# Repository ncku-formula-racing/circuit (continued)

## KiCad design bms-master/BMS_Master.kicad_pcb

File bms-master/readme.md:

# BMS Master board PCB
NCKU Formula racing 2025  
BMS Master using TI's BQ79600-Q1 as communication module and STM32F103C8T6 as MCU

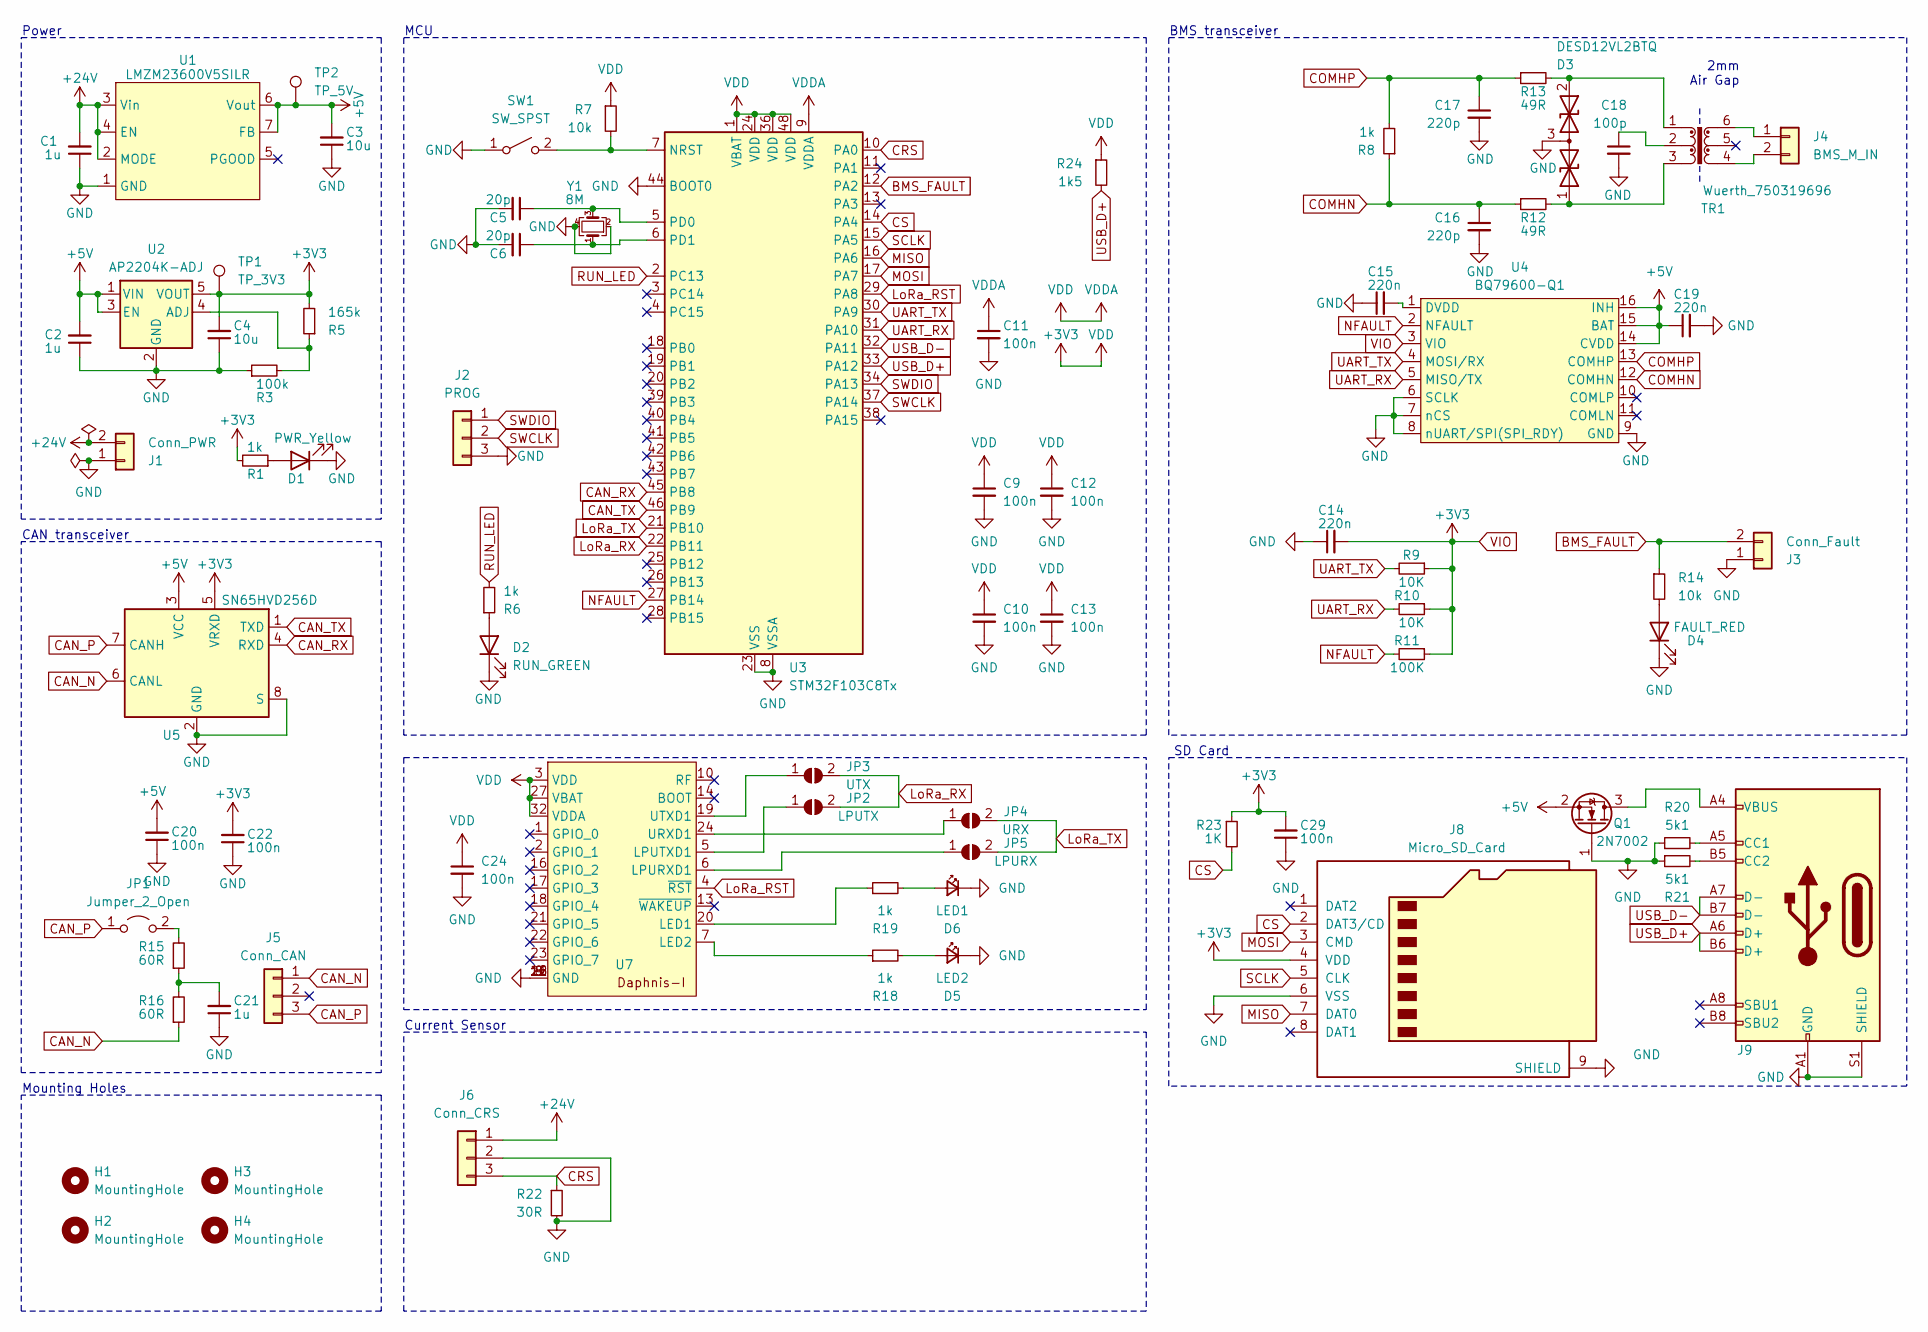
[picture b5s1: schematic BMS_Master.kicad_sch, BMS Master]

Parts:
C1, C2, C21: 1u; C_0603_1608Metric
C3, C4: 10u; C_0805_2012Metric
C5, C6: 20p; C_0603_1608Metric
C9, C10, C11, C12, C13, C20, C22, C24, C29: 100n; C_0603_1608Metric
C14, C15, C19: 220n; C_0603_1608Metric
C16, C17: 220p; C_0603_1608Metric
C18: 100p; C_0603_1608Metric
D1: PWR_Yellow; LED_0805_2012Metric
D2: RUN_GREEN; LED_0805_2012Metric
D3: DESD12VL2BTQ; SOT-23
D4: FAULT_RED; LED_0805_2012Metric
D5: LED2; LED_0805_2012Metric
D6: LED1; LED_0805_2012Metric
H1, H2, H3, H4: MountingHole; MountingHole_3.2mm_M3_DIN965
J1: Conn_PWR; JST_XH_B2B-XH-A_1x02_P2.50mm_Vertical
J2: PROG; PinHeader_1x03_P2.54mm_Vertical
J3: Conn_Fault; JST_XH_B2B-XH-A_1x02_P2.50mm_Vertical
J4: BMS_M_IN; Molex_Micro-Fit_3.0_43650-0200_1x02_P3.00mm_Horizontal
J5: Conn_CAN; JST_XH_B3B-XH-A_1x03_P2.50mm_Vertical
J6: Conn_CRS; JST_XH_B3B-XH-A_1x03_P2.50mm_Vertical
J8: Micro_SD_Card; microSD_HC_Molex_47219-2001
J9: USB_C_Receptacle_USB2.0_16P; USB_C_Receptacle_Palconn_UTC16-G
JP1: Jumper_2_Open; TestPoint_2Pads_Pitch2.54mm_Drill0.8mm
JP2: LPUTX; SolderJumper-2_P1.3mm_Open_RoundedPad1.0x1.5mm
JP3: UTX; SolderJumper-2_P1.3mm_Open_RoundedPad1.0x1.5mm
JP4: URX; SolderJumper-2_P1.3mm_Open_RoundedPad1.0x1.5mm
JP5: LPURX; SolderJumper-2_P1.3mm_Open_RoundedPad1.0x1.5mm
Q1: 2N7002; SOT-23
R1, R6, R8, R18, R19: 1k; R_0603_1608Metric
R3: 100k; R_0603_1608Metric
R5: 165k; R_0603_1608Metric
R7, R14: 10k; R_0603_1608Metric
R9, R10: 10K; R_0603_1608Metric
R11: 100K; R_0603_1608Metric
R12, R13: 49R; R_0603_1608Metric
R15, R16: 60R; R_0603_1608Metric
R20, R21: 5k1; R_0603_1608Metric_Pad0.98x0.95mm_HandSolder
R22: 30R; R_0603_1608Metric
R23: 1K; R_0603_1608Metric
R24: 1k5; R_0603_1608Metric
SW1: SW_SPST; SW_SPST_FSMSM
TP1: TP_3V3; Pin_D1.0mm_L10.0mm
TP2: TP_5V; Pin_D1.0mm_L10.0mm
TR1: Wuerth_750319696; Transformer_Wuerth_750315371
U1: LMZM23600V5SILR; MODULE_LMZM23601V5SILR
U2: AP2204K-ADJ; SOT-23-5
U3: STM32F103C8Tx; LQFP-48_7x7mm_P0.5mm
U4: BQ79600-Q1; TSSOP-16_4.4x5mm_P0.65mm
U5: SN65HVD256D; SOIC-8_3.9x4.9mm_P1.27mm
U7: Daphnis-I
Y1: 8M; Crystal_SMD_SeikoEpson_FA238-4Pin_3.2x2.5mm

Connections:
+5V: C2.2, C3.2, C19.1, C20.2, Q1.2 (S), TP2.1, U1.6 (Vout), U1.7 (FB), U2.1 (VIN), U2.3 (EN), U4.14 (CVDD), U4.15 (BAT), U4.16 (INH), U5.3 (VCC)
+24V: C1.2, J1.2, J6.1, U1.2 (MODE), U1.3 (Vin), U1.4 (EN)
BMS_FAULT: J3.2, R14.1, U3.12 (PA2)
CAN_N: J5.1, R16.1, U5.6 (CANL)
CAN_P: J5.3, JP1.1 (A), U5.7 (CANH)
CAN_RX: U3.45 (PB8), U5.4 (RXD)
CAN_TX: U3.46 (PB9), U5.1 (TXD)
COMHN: C16.1, R8.1, R12.1, U4.12 (COMHN)
COMHP: C17.1, R8.2, R13.1, U4.13 (COMHP)
CRS: J6.3, R22.1, U3.10 (PA0)
CS: J8.2 (DAT3/CD), R23.2, U3.14 (PA4)
GND: C1.1, C2.1, C3.1, C4.1, C5.2, C6.2, C9.2, C10.2, C11.2, C12.2, C13.2, C14.1, C15.1, C16.2, C17.2, C18.2, C19.2, C20.1, C21.1, C22.1, C24.2, C29.1, D1.1 (K), D2.1 (K), D3.3 (common), D4.1 (K), D5.1 (K), D6.1 (K), J1.1, J2.3, J3.1, J6.2, J8.6 (VSS), J8.9 (SHIELD), J9.A1 (GND), J9.A12 (GND), J9.B1 (GND), J9.B12 (GND), J9.S1 (SHIELD), Q1.1 (G), R3.1, R20.1, R21.1, R22.2, SW1.1 (A), U1.1 (GND), U1.11, U2.2 (GND), U3.8 (VSSA), U3.23 (VSS), U3.35 (VSS), U3.44 (BOOT0), U3.47 (VSS), U4.6 (SCLK), U4.7 (nCS), U4.8 (nUART/SPI(SPI_RDY)), U4.9 (GND), U5.2 (GND), U5.8 (S), U7.8 (GND), U7.9 (GND), U7.11 (GND), U7.12 (GND), U7.15 (GND), U7.26 (GND), Y1.2, Y1.4
LoRa_RST: U3.29 (PA8), U7.4 (~RST)
LoRa_RX: JP2.2 (B), JP3.2 (B), U3.22 (PB11)
LoRa_TX: JP4.2 (B), JP5.2 (B), U3.21 (PB10)
MISO: J8.7 (DAT0), U3.16 (PA6)
MOSI: J8.3 (CMD), U3.17 (PA7)
NFAULT: R11.2, U3.27 (PB14), U4.2 (NFAULT)
unnamed: C18.1, TR1.2
unnamed: C21.2, R15.1, R16.2
unnamed: D1.2 (A), R1.1
unnamed: D2.2 (A), R6.1
unnamed: D3.1 (A1), R12.2, TR1.3
unnamed: D3.2 (A2), R13.2, TR1.1
unnamed: D4.2 (A), R14.2
unnamed: D5.2 (A), R18.2
unnamed: D6.2 (A), R19.2
unnamed: J4.1, TR1.6
unnamed: J4.2, TR1.4
unnamed: J9.A5 (CC1), R20.2
unnamed: J9.B5 (CC2), R21.2
unnamed: JP1.2 (B), R15.2
unnamed: JP2.1 (A), U7.5 (LPUTXD1)
unnamed: JP3.1 (A), U7.19 (UTXD1)
unnamed: JP4.1 (A), U7.24 (URXD1)
unnamed: JP5.1 (A), U7.6 (LPURXD1)
unnamed: J9.A4 (VBUS), J9.A9 (VBUS), J9.B4 (VBUS), J9.B9 (VBUS), Q1.3 (D)
unnamed: R7.2, SW1.2 (B), U3.7 (NRST)
unnamed: R3.2, R5.1, U2.4 (ADJ)
unnamed: C5.1, U3.5 (PD0), Y1.3
unnamed: C6.1, U3.6 (PD1), Y1.1
unnamed: C15.2, U4.1 (DVDD)
unnamed: R19.1, U7.20 (LED1)
unnamed: R18.1, U7.7 (LED2)
RUN_LED: R6.2, U3.2 (PC13)
SCLK: J8.5 (CLK), U3.15 (PA5)
SWCLK: J2.2, U3.37 (PA14)
SWDIO: J2.1, U3.34 (PA13)
UART_RX: R10.2, U3.31 (PA10), U4.5 (MISO/TX)
UART_TX: R9.2, U3.30 (PA9), U4.4 (MOSI/RX)
USB_D+: J9.A6 (D+), J9.B6 (D+), R24.2, U3.33 (PA12)
USB_D-: J9.A7 (D-), J9.B7 (D-), U3.32 (PA11)
VIO: C4.2, C9.1, C10.1, C11.1, C12.1, C13.1, C14.2, C22.2, C24.1, C29.2, J8.4 (VDD), R1.2, R5.2, R7.1, R9.1, R10.1, R11.1, R23.1, R24.1, TP1.1, U2.5 (VOUT), U3.1 (VBAT), U3.9 (VDDA), U3.24 (VDD), U3.36 (VDD), U3.48 (VDD), U4.3 (VIO), U5.5 (VRXD), U7.3 (VDD), U7.27 (VBAT), U7.32 (VDDA)

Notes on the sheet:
MCU
SD Card
2mm Air Gap
Current Sensor
Mounting Holes
BMS transceiver
Power
CAN transceiver

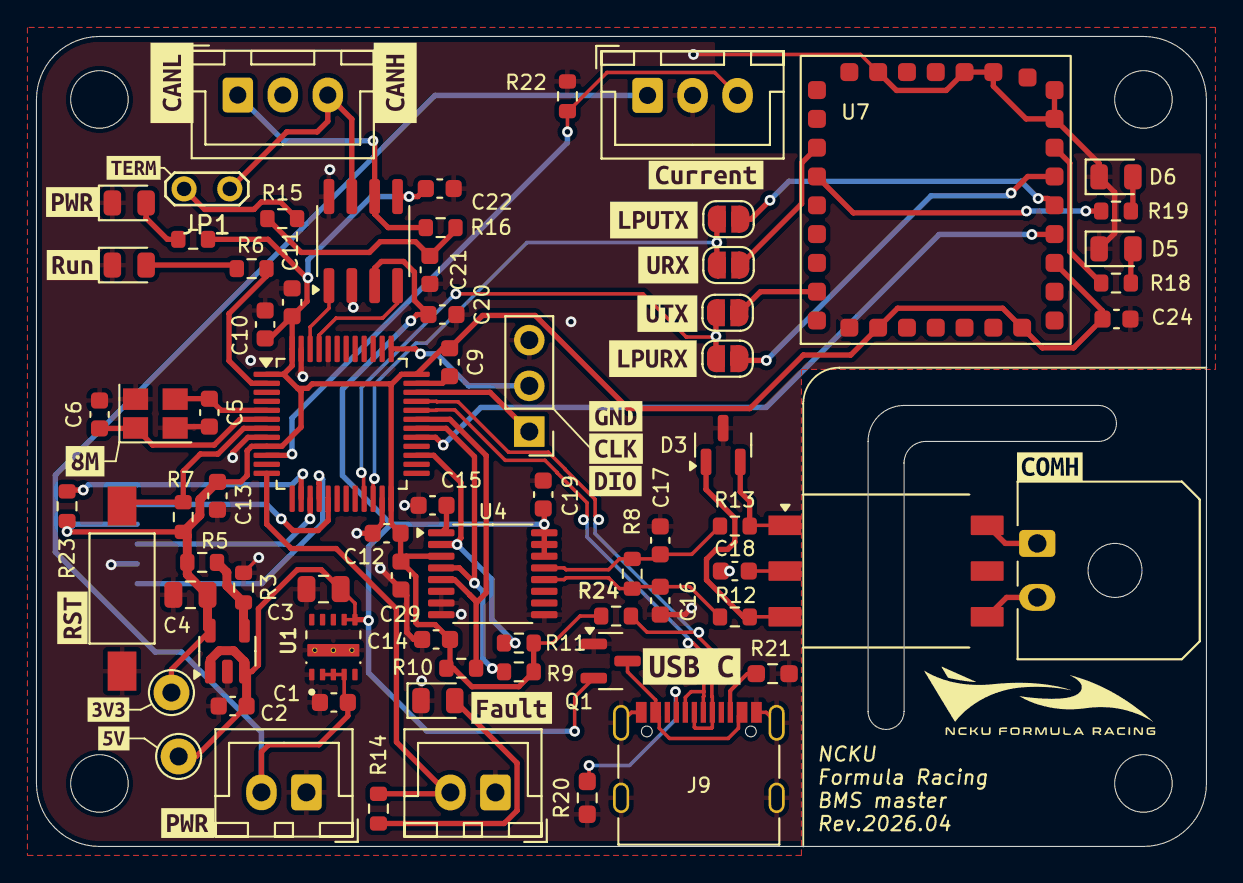
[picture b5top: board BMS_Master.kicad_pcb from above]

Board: 2 copper layers, 65.0 x 45.0 mm, 99 parts (1 on the bottom side), 53 nets.

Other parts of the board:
kibuzzard-67D6AC10: G***; kibuzzard-67D6AC10
kibuzzard-68BABEC4: G***; kibuzzard-68BABEC4
kibuzzard-68BABEE5: G***; kibuzzard-68BABEE5
kibuzzard-68BABEF1: G***; kibuzzard-68BABEF1
kibuzzard-68BABF14: G***; kibuzzard-68BABF14
kibuzzard-69EA7393: G***; kibuzzard-69EA7393
kibuzzard-69EB13FF: G***; kibuzzard-69EB13FF
kibuzzard-69EB1406: G***; kibuzzard-69EB1406
kibuzzard-679F52AD: G***; kibuzzard-679F52AD
kibuzzard-679F52BD: G***; kibuzzard-679F52BD
kibuzzard-679F55F7: G***; kibuzzard-679F55F7
kibuzzard-679F56A0: G***; kibuzzard-679F56A0
kibuzzard-679F56A8: G***; kibuzzard-679F56A8
kibuzzard-679F561D: G***; kibuzzard-679F561D
kibuzzard-679F5580: G***; kibuzzard-679F5580
kibuzzard-679F5696: G***; kibuzzard-679F5696
kibuzzard-68838A70: G***; kibuzzard-68838A70
kibuzzard-68838B09: G***; kibuzzard-68838B09
kibuzzard-68838DBE: G***; kibuzzard-68838DBE
kibuzzard-68838DC4: G***; kibuzzard-68838DC4
kibuzzard-68838E18: G***; kibuzzard-68838E18

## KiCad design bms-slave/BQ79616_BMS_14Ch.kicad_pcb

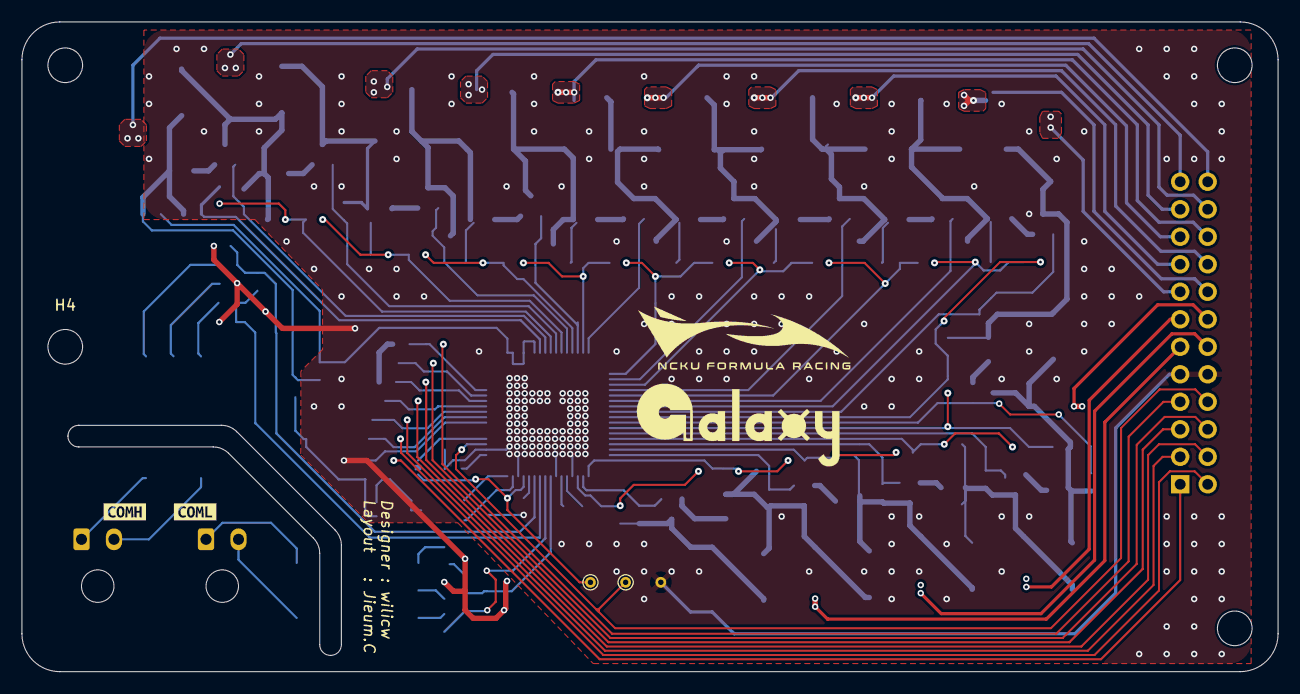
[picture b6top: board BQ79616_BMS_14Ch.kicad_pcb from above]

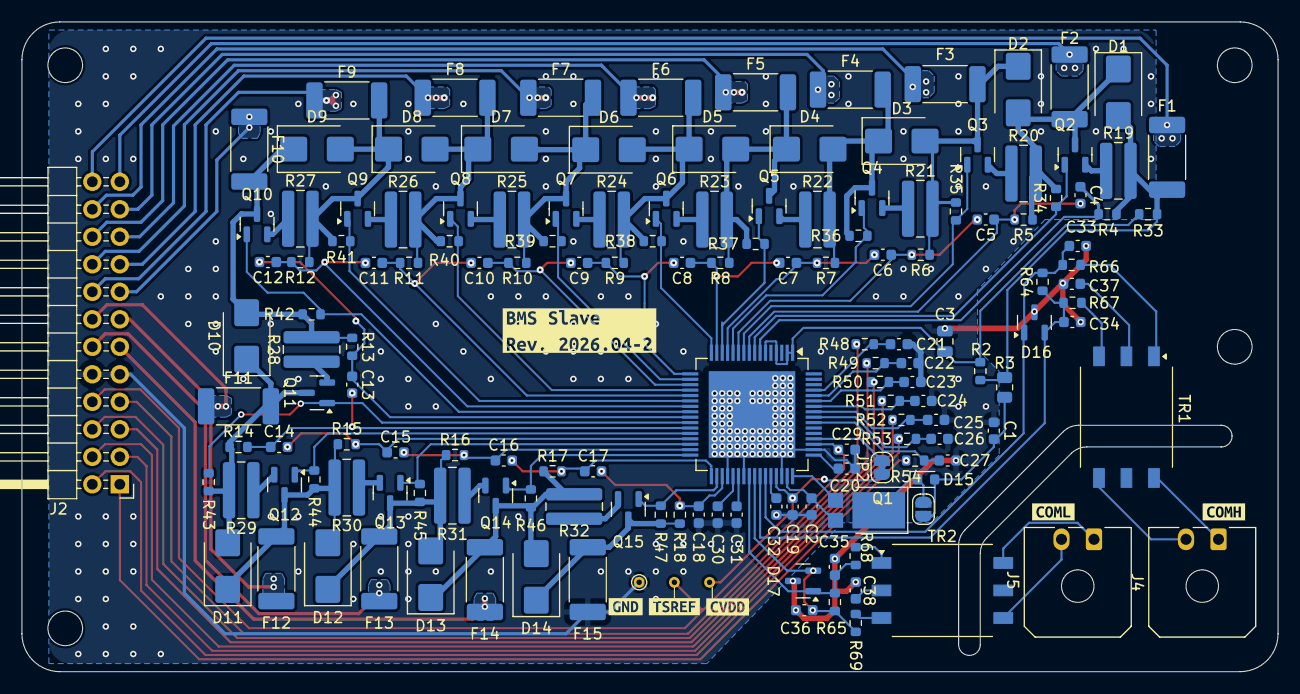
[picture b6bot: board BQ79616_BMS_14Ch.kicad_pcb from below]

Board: 4 copper layers, 116.0 x 60.0 mm, 166 parts (158 on the bottom side), 113 nets.

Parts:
C1: 220n/100V; C_0603_1608Metric
C2, C21, C22, C23, C24, C25, C26, C27, C32: 100n; C_0603_1608Metric
C3: 10u; C_0805_2012Metric
C4, C5, C6, C7, C8, C9, C10, C11, C12, C13, C14, C15, C16, C17, C18: 470n; C_0603_1608Metric
C19: 4.7u; C_0603_1608Metric
C20: 2.2u; C_0603_1608Metric
C29, C30, C31: 1u; C_0603_1608Metric
C33, C34, C35, C36: 220p; C_0603_1608Metric
C37, C38: 100p; C_0603_1608Metric
D1, D2, D3, D4, D5, D6, D7, D8, D9, D10, D11, D12, D13, D14: SMBJ55.0CA; D_SMB
D15: LED_PWR; LED_0603_1608Metric
D16, D17: DESD12VL2BTQ; SOT-23
F1, F2, F3, F4, F5, F6, F7, F8, F9, F10, F11, F12, F13, F14, F15: 0.5A Fuse; Fuse_2512_6332Metric_Pad1.52x3.35mm_HandSolder
H1, H2, H3, H4: M3; MountingHole_3.2mm_M3_ISO7380
J2: Conn_02x12_Odd_Even; PinHeader_2x12_P2.54mm_Horizontal
J4: BMS_A_OUT; Molex_Micro-Fit_3.0_43650-0200_1x02_P3.00mm_Horizontal
J5: BMS_A_IN; Molex_Micro-Fit_3.0_43650-0200_1x02_P3.00mm_Horizontal
JP1: SJ_BYPASS; SolderJumper-2_P1.3mm_Open_RoundedPad1.0x1.5mm
JP2: SolderJumper_2_Bridged; SolderJumper-2_P1.3mm_Bridged_RoundedPad1.0x1.5mm
Q1: DXT5551P5; D_PowerDI-5
Q2, Q3, Q4, Q5, Q6, Q7, Q8, Q9, Q10, Q11, Q12, Q13, Q14, Q15: DMN2024UQ; SOT-23
R2: 30R; R_0603_1608Metric
R3: 100R; R_0805_2012Metric
R4, R5, R6, R7, R8, R9, R10, R11, R12, R13, R14, R15, R16, R17, R18: 100R; R_0603_1608Metric
R19, R20, R21, R22, R23, R24, R25, R26, R27, R28, R29, R30, R31, R32: 20R/1W; R_1020_2550Metric
R33, R34, R35, R36, R37, R38, R39, R40, R41, R42, R43, R44, R45, R46, R47, R48, R49, R50, R51, R52, R53, R54, R64, R65: 1k; R_0603_1608Metric
R66, R67, R68, R69: 49R; R_0603_1608Metric
TP2: TP_CVDD; TestPoint_THTPad_D1.0mm_Drill0.5mm
TP3: TP_GND; TestPoint_THTPad_D1.0mm_Drill0.5mm
TP4: TP_TSREF; TestPoint_THTPad_D1.0mm_Drill0.5mm
TR1, TR2: Wuerth_750319696; Transformer_Wuerth_750315371
U1: HTQFP-64-1EP_10x10mm_P0.5mm_EP8x8mm
kibuzzard-67C80B8B: G***; kibuzzard-67C80B8B
kibuzzard-67C80B29, kibuzzard-67C80B29#2: G***; kibuzzard-67C80B29
kibuzzard-69D6BEF3, kibuzzard-69D6BEF3#2: G***; kibuzzard-69D6BEF3
kibuzzard-69DFF7FB: G***; kibuzzard-69DFF7FB
kibuzzard-69DFF833: G***; kibuzzard-69DFF833
kibuzzard-69F31310: G***; kibuzzard-69F31310

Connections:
/AVDD_A: C31.1, U1.38 (AVDD)
/BAT_A: C3.2, R2.2, R33.2, U1.1 (BAT), U1.2 (CB16), U1.4 (CB15), U1.6 (CB14)
/CB_A0: Q15.1 (G), R47.2, U1.34 (CB0)
/CB_A1: Q14.1 (G), R46.2, U1.32 (CB1)
/CB_A2: Q13.1 (G), R45.2, U1.30 (CB2)
/CB_A3: Q12.1 (G), R44.2, U1.28 (CB3)
/CB_A4: Q11.1 (G), R43.2, U1.26 (CB4)
/CB_A5: Q10.1 (G), R42.2, U1.24 (CB5)
/CB_A6: Q9.1 (G), R41.2, U1.22 (CB6)
/CB_A7: Q8.1 (G), R40.2, U1.20 (CB7)
/CB_A8: Q7.1 (G), R39.2, U1.18 (CB8)
/CB_A9: Q6.1 (G), R38.2, U1.16 (CB9)
/CB_A10: Q5.1 (G), R37.2, U1.14 (CB10)
/CB_A11: Q4.1 (G), R36.2, U1.12 (CB11)
/CB_A12: Q3.1 (G), R35.2, U1.10 (CB12)
/CB_A13: Q2.1 (G), R34.2, U1.8 (CB13)
/CELL_A1: F14.1, J2.11
/CELL_A2: F13.1, J2.12
/CELL_A3: F12.1, J2.13
/CELL_A4: F11.1, J2.14
/CELL_A5: F10.1, J2.15
/CELL_A6: F9.1, J2.16
/CELL_A7: F8.1, J2.17
/CELL_A8: F7.1, J2.18
/CELL_A9: F6.1, J2.19
/CELL_A10: F5.1, J2.20
/CELL_A11: F4.1, J2.21
/CELL_A12: F3.1, J2.22
/CELL_A13: F2.1, J2.23
/CELL_A14: F1.1, J2.24
/COMHN: C34.1, D16.2 (A2), R64.2, R67.1, U1.42 (COMHN)
/COMHP: C33.1, D16.1 (A1), R64.1, R66.1, U1.43 (COMHP)
/COMLN: C36.1, D17.2 (A2), R65.2, R69.1, U1.41 (COMLN)
/COMLP: C35.1, D17.1 (A1), R65.1, R68.1, U1.40 (COMLP)
/CVDD_A: C19.1, JP2.1 (A), TP2.1, U1.45 (CVDD)
/DVDD_A: C20.1, U1.49 (DVDD)
/GPIO_A1: C21.1, R48.1, U1.61 (GPIO1)
/GPIO_A2: C22.1, R49.1, U1.60 (GPIO2)
/GPIO_A3: C23.1, R50.1, U1.59 (GPIO3)
/GPIO_A4: C24.1, R51.1, U1.58 (GPIO4)
/GPIO_A5: C25.1, R52.1, U1.57 (GPIO5)
/GPIO_A6: C26.1, R53.1, U1.56 (GPIO6)
/GPIO_A7: C27.1, R54.1, U1.55 (GPIO7)
/LDOIN_A: C2.2, Q1.3 (E), U1.47 (LDOIN)
/NEG5V_A: C32.1, U1.44 (NEG5V)
/NPNB_A: Q1.2 (B), U1.48 (NPNB)
/NTC01: J2.7, R48.2
/NTC02: J2.6, R49.2
/NTC03: J2.5, R50.2
/NTC04: J2.4, R51.2
/NTC05: J2.3, R52.2
/NTC06: J2.2, R53.2
/NTC07: J2.1, R54.2
/REFHP_A: C30.1, U1.37 (REFHP)
/RX_A: JP2.2 (B), U1.52 (RX)
/TSREF_A: C29.1, J2.8, TP4.1, U1.51 (TSREF)
/VC_A0: C17.2, C18.1, R18.2, U1.35 (VC0)
/VC_A1: C16.2, C17.1, R17.2, U1.33 (VC1)
/VC_A2: C15.2, C16.1, R16.2, U1.31 (VC2)
/VC_A3: C14.2, C15.1, R15.2, U1.29 (VC3)
/VC_A4: C13.2, C14.1, R14.2, U1.27 (VC4)
/VC_A5: C12.2, C13.1, R13.2, U1.25 (VC5)
/VC_A6: C11.2, C12.1, R12.2, U1.23 (VC6)
/VC_A7: C10.2, C11.1, R11.2, U1.21 (VC7)
/VC_A8: C9.2, C10.1, R10.2, U1.19 (VC8)
/VC_A9: C8.2, C9.1, R9.2, U1.17 (VC9)
/VC_A10: C7.2, C8.1, R8.2, U1.15 (VC10)
/VC_A11: C6.2, C7.1, R7.2, U1.13 (VC11)
/VC_A12: C5.2, C6.1, R6.2, U1.11 (VC12)
/VC_A13: C4.2, C5.1, R5.2, U1.9 (VC13)
/VC_A14: C4.1, R4.2, U1.7 (VC14)
GND1: C1.1, C2.1, C3.1, C18.2, C19.2, C20.2, C21.2, C22.2, C23.2, C24.2, C25.2, C26.2, C27.2, C29.2, C30.2, C31.2, C32.2, C33.2, C34.2, C35.2, C36.2, C37.2, C38.2, D16.3 (common), D17.3 (common), F15.1, J2.9, J2.10, TP3.1, U1.36 (REFHM), U1.39 (AVSS), U1.46 (CVSS), U1.50 (GND), U1.65 (PAD)
unnamed: C37.1, TR1.2
unnamed: C38.1, TR2.2
unnamed: D1.1 (A1), D2.2 (A2), F2.2, Q2.3 (S), R5.1, R20.1, R34.1
unnamed: D1.2 (A2), F1.2, R2.1, R3.1, R4.1, R19.1, R33.1
unnamed: D2.1 (A1), D3.2 (A2), F3.2, Q3.3 (S), R6.1, R21.1, R35.1
unnamed: D3.1 (A1), D4.2 (A2), F4.2, Q4.3 (S), R7.1, R22.1, R36.1
unnamed: D4.1 (A1), D5.2 (A2), F5.2, Q5.3 (S), R8.1, R23.1, R37.1
unnamed: D5.1 (A1), D6.2 (A2), F6.2, Q6.3 (S), R9.1, R24.1, R38.1
unnamed: D6.1 (A1), D7.2 (A2), F7.2, Q7.3 (S), R10.1, R25.1, R39.1
unnamed: D7.1 (A1), D8.2 (A2), F8.2, Q8.3 (S), R11.1, R26.1, R40.1
unnamed: D8.1 (A1), D9.2 (A2), F9.2, Q9.3 (S), R12.1, R27.1, R41.1
unnamed: D10.1 (A1), D11.2 (A2), F11.2, Q11.3 (S), R14.1, R29.1, R43.1
unnamed: D9.1 (A1), D10.2 (A2), F10.2, Q10.3 (S), R13.1, R28.1, R42.1
unnamed: D11.1 (A1), D12.2 (A2), F12.2, Q12.3 (S), R15.1, R30.1, R44.1
unnamed: D12.1 (A1), D13.2 (A2), F13.2, Q13.3 (S), R16.1, R31.1, R45.1
unnamed: D13.1 (A1), D14.2 (A2), F14.2, Q14.3 (S), R17.1, R32.1, R46.1
unnamed: D14.1 (A1), F15.2, Q15.3 (S), R18.1, R47.1
unnamed: C1.2, D15.2 (A), JP1.1 (A), R3.2
unnamed: D15.1 (K), JP1.2 (B), Q1.1 (C)
unnamed: J4.1, TR1.6
unnamed: J4.2, TR1.4
unnamed: J5.1, TR2.6
unnamed: J5.2, TR2.4
unnamed: Q2.2 (D), R19.2
unnamed: Q3.2 (D), R20.2
unnamed: Q4.2 (D), R21.2
unnamed: Q5.2 (D), R22.2
unnamed: Q6.2 (D), R23.2
unnamed: Q7.2 (D), R24.2
unnamed: Q8.2 (D), R25.2
unnamed: Q9.2 (D), R26.2
unnamed: Q10.2 (D), R27.2
unnamed: Q11.2 (D), R28.2
unnamed: Q12.2 (D), R29.2
unnamed: Q13.2 (D), R30.2
unnamed: Q14.2 (D), R31.2
unnamed: Q15.2 (D), R32.2
unnamed: R66.2, TR1.1
unnamed: R67.2, TR1.3
unnamed: R68.2, TR2.1
unnamed: R69.2, TR2.3

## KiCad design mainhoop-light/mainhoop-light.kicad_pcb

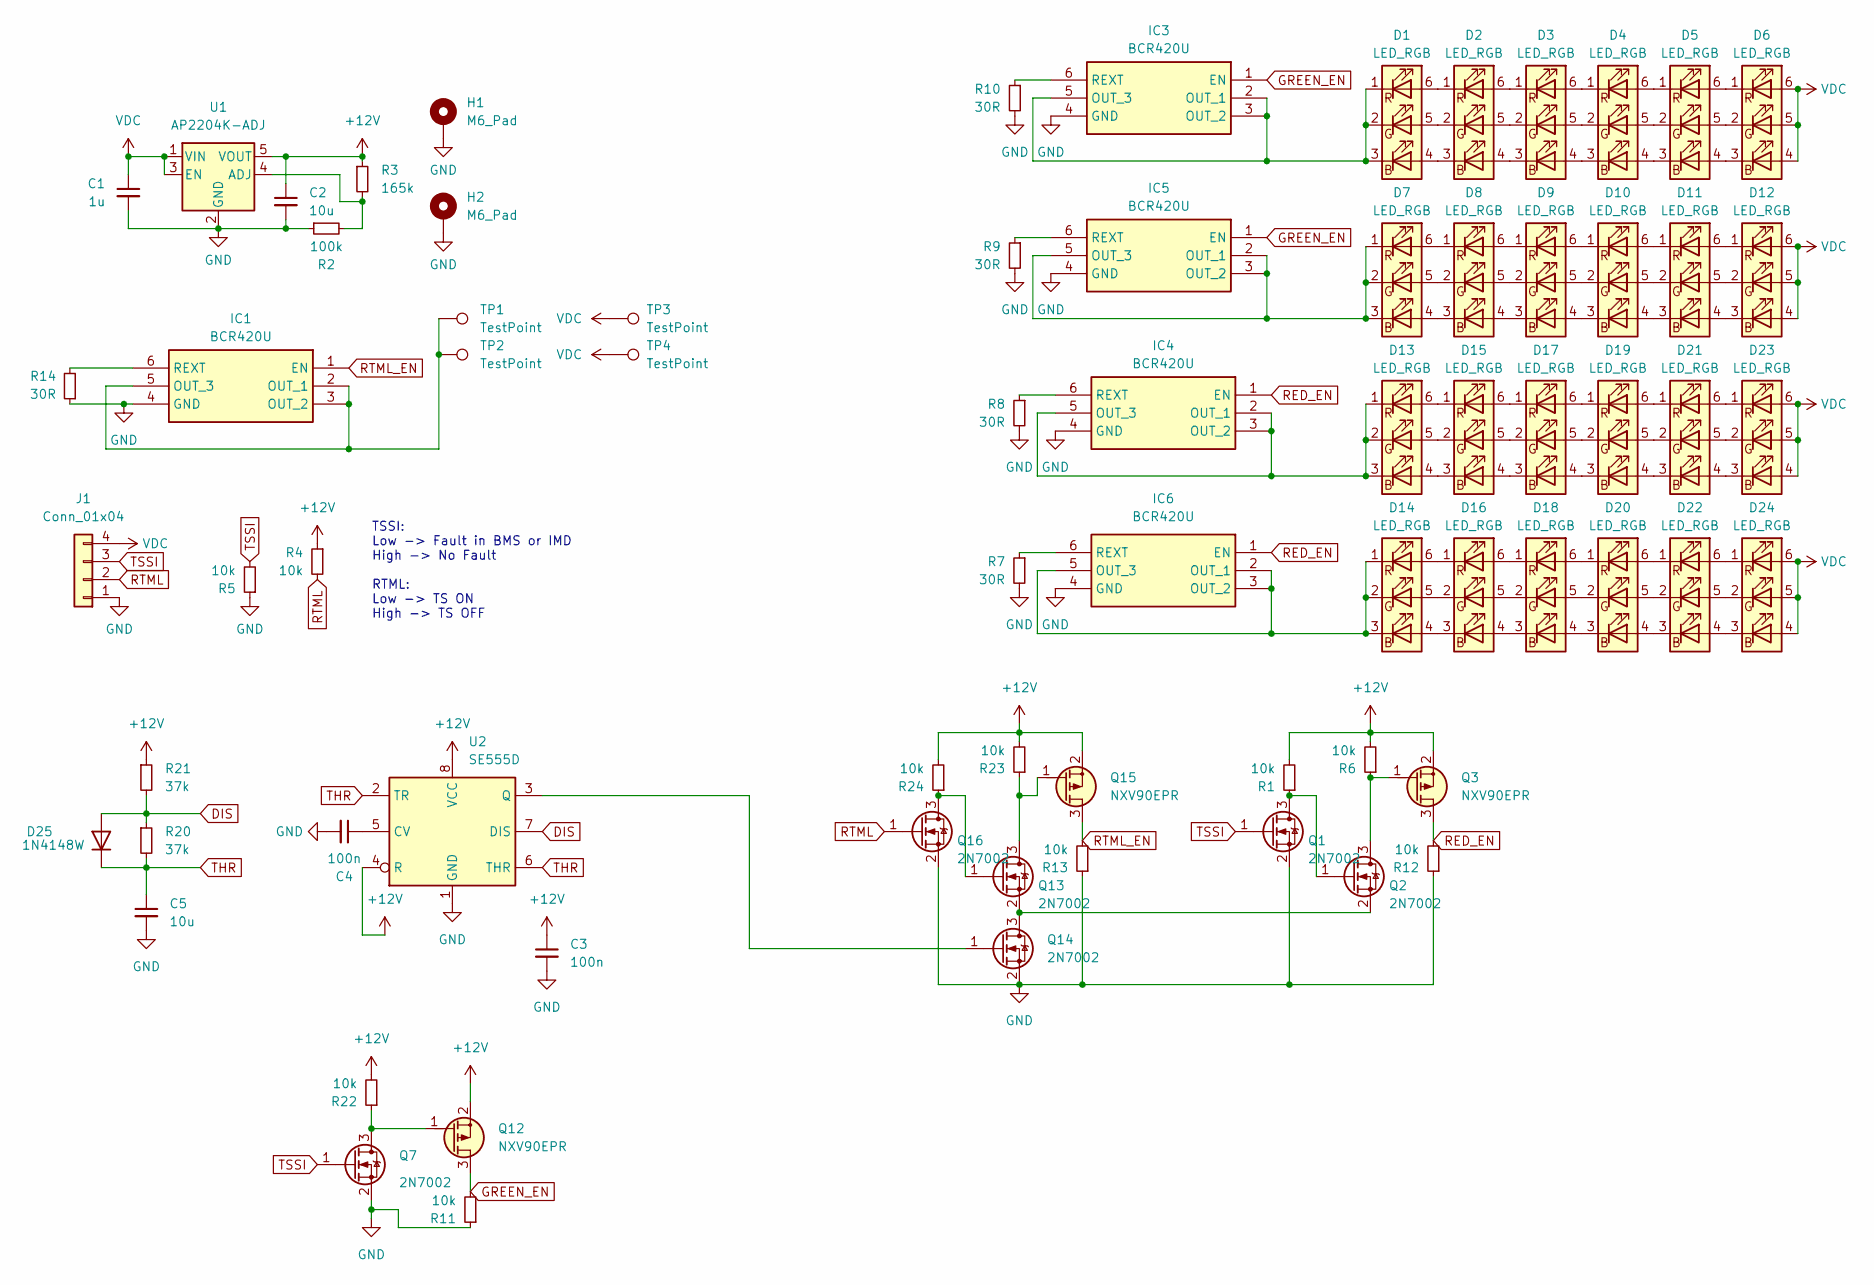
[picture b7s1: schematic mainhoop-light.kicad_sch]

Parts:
C1: 1u; C_0603_1608Metric
C2, C5: 10u; C_0805_2012Metric
C3, C4: 100n; C_0603_1608Metric
D1, D2, D3, D4, D5, D6, D7, D8, D9, D10, D11, D12, D13, D14, D15, D16, D17, D18, D19, D20, D21, D22, D23, D24: LED_RGB; LED_RGB_5050-6
D25: 1N4148W; D_SOD-123
H1, H2: M6_Pad; MountingHole_4mm_Pad_TopBottom
IC1, IC3, IC4, IC5, IC6: BCR420U; SOT-23-6; Mouser Part Number 621-BCR420UW6-7
J1: Conn_01x04; JST_XH_B4B-XH-A_1x04_P2.50mm_Vertical
Q1, Q2, Q7, Q13, Q14, Q16: 2N7002; SOT-23
Q3, Q12, Q15: NXV90EPR; SOT-23-3
R1, R4, R5, R6, R11, R12, R13, R22, R23, R24: 10k; R_0603_1608Metric
R2: 100k; R_0603_1608Metric
R3: 165k; R_0603_1608Metric
R7, R8, R9, R10, R14: 30R; R_0603_1608Metric
R20, R21: 37k; R_0603_1608Metric
TP1, TP2, TP3, TP4: TestPoint; Pin_D1.3mm_L11.0mm
U1: AP2204K-ADJ; SOT-23-5
U2: SE555D; SOIC-8_3.9x4.9mm_P1.27mm

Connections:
+12V: C2.1, C3.1, Q3.2 (S), Q12.2 (S), Q15.2 (S), R1.2, R3.1, R4.1, R6.2, R21.1, R22.2, R23.2, R24.2, U1.5 (VOUT), U2.4 (R), U2.8 (VCC)
DIS: D25.2 (A), R20.1, R21.2, U2.7 (DIS)
GND: C1.2, C2.2, C3.2, C4.2, C5.2, H1.1, H2.1, IC1.4 (GND), IC3.4 (GND), IC4.4 (GND), IC5.4 (GND), IC6.4 (GND), J1.1, Q1.2 (S), Q7.2 (S), Q14.2 (S), Q16.2 (S), R2.1, R5.1, R7.2, R8.2, R9.2, R10.2, R11.1, R12.1, R13.1, R14.1, U1.2 (GND), U2.1 (GND)
GREEN_EN: IC3.1 (EN), IC5.1 (EN), Q12.3 (D), R11.2
unnamed: D1.4 (BA), D2.3 (BK)
unnamed: D1.1 (RK), D1.2 (GK), D1.3 (BK), IC3.2 (OUT_1), IC3.3 (OUT_2), IC3.5 (OUT_3)
unnamed: D1.5 (GA), D2.2 (GK)
unnamed: D1.6 (RA), D2.1 (RK)
unnamed: D2.4 (BA), D3.3 (BK)
unnamed: D2.5 (GA), D3.2 (GK)
unnamed: D2.6 (RA), D3.1 (RK)
unnamed: D3.4 (BA), D4.3 (BK)
unnamed: D3.5 (GA), D4.2 (GK)
unnamed: D3.6 (RA), D4.1 (RK)
unnamed: D4.4 (BA), D5.3 (BK)
unnamed: D4.5 (GA), D5.2 (GK)
unnamed: D4.6 (RA), D5.1 (RK)
unnamed: D5.4 (BA), D6.3 (BK)
unnamed: D5.5 (GA), D6.2 (GK)
unnamed: D5.6 (RA), D6.1 (RK)
unnamed: D7.4 (BA), D8.3 (BK)
unnamed: D7.1 (RK), D7.2 (GK), D7.3 (BK), IC5.2 (OUT_1), IC5.3 (OUT_2), IC5.5 (OUT_3)
unnamed: D7.5 (GA), D8.2 (GK)
unnamed: D7.6 (RA), D8.1 (RK)
unnamed: D8.4 (BA), D9.3 (BK)
unnamed: D8.5 (GA), D9.2 (GK)
unnamed: D8.6 (RA), D9.1 (RK)
unnamed: D10.4 (BA), D11.3 (BK)
unnamed: D9.4 (BA), D10.3 (BK)
unnamed: D10.5 (GA), D11.2 (GK)
unnamed: D9.5 (GA), D10.2 (GK)
unnamed: D10.6 (RA), D11.1 (RK)
unnamed: D9.6 (RA), D10.1 (RK)
unnamed: D11.4 (BA), D12.3 (BK)
unnamed: D11.5 (GA), D12.2 (GK)
unnamed: D11.6 (RA), D12.1 (RK)
unnamed: D13.4 (BA), D15.3 (BK)
unnamed: D13.1 (RK), D13.2 (GK), D13.3 (BK), IC4.2 (OUT_1), IC4.3 (OUT_2), IC4.5 (OUT_3)
unnamed: D13.5 (GA), D15.2 (GK)
unnamed: D13.6 (RA), D15.1 (RK)
unnamed: D14.4 (BA), D16.3 (BK)
unnamed: D14.1 (RK), D14.2 (GK), D14.3 (BK), IC6.2 (OUT_1), IC6.3 (OUT_2), IC6.5 (OUT_3)
unnamed: D14.5 (GA), D16.2 (GK)
unnamed: D14.6 (RA), D16.1 (RK)
unnamed: D15.4 (BA), D17.3 (BK)
unnamed: D15.5 (GA), D17.2 (GK)
unnamed: D15.6 (RA), D17.1 (RK)
unnamed: D16.4 (BA), D18.3 (BK)
unnamed: D16.5 (GA), D18.2 (GK)
unnamed: D16.6 (RA), D18.1 (RK)
unnamed: D17.4 (BA), D19.3 (BK)
unnamed: D17.5 (GA), D19.2 (GK)
unnamed: D17.6 (RA), D19.1 (RK)
unnamed: D18.4 (BA), D20.3 (BK)
unnamed: D18.5 (GA), D20.2 (GK)
unnamed: D18.6 (RA), D20.1 (RK)
unnamed: D19.4 (BA), D21.3 (BK)
unnamed: D19.5 (GA), D21.2 (GK)
unnamed: D19.6 (RA), D21.1 (RK)
unnamed: D20.4 (BA), D22.3 (BK)
unnamed: D20.5 (GA), D22.2 (GK)
unnamed: D20.6 (RA), D22.1 (RK)
unnamed: D21.4 (BA), D23.3 (BK)
unnamed: D21.5 (GA), D23.2 (GK)
unnamed: D21.6 (RA), D23.1 (RK)
unnamed: D22.4 (BA), D24.3 (BK)
unnamed: D22.5 (GA), D24.2 (GK)
unnamed: D22.6 (RA), D24.1 (RK)
unnamed: IC1.2 (OUT_1), IC1.3 (OUT_2), IC1.5 (OUT_3), TP1.1, TP2.1
unnamed: IC1.6 (REXT), R14.2
unnamed: IC3.6 (REXT), R10.1
unnamed: IC4.6 (REXT), R8.1
unnamed: IC5.6 (REXT), R9.1
unnamed: IC6.6 (REXT), R7.1
unnamed: Q1.3 (D), Q2.1 (G), R1.1
unnamed: Q2.3 (D), Q3.1 (G), R6.1
unnamed: Q7.3 (D), Q12.1 (G), R22.1
unnamed: Q13.3 (D), Q15.1 (G), R23.1
unnamed: Q13.1 (G), Q16.3 (D), R24.1
unnamed: Q2.2 (S), Q13.2 (S), Q14.3 (D)
unnamed: Q14.1 (G), U2.3 (Q)
unnamed: R2.2, R3.2, U1.4 (ADJ)
unnamed: C4.1, U2.5 (CV)
RED_EN: IC4.1 (EN), IC6.1 (EN), Q3.3 (D), R12.2
RTML: J1.2, Q16.1 (G), R4.2
RTML_EN: IC1.1 (EN), Q15.3 (D), R13.2
THR: C5.1, D25.1 (K), R20.2, U2.2 (TR), U2.6 (THR)
TSSI: J1.3, Q1.1 (G), Q7.1 (G), R5.2
VDC: C1.1, D6.4 (BA), D6.5 (GA), D6.6 (RA), D12.4 (BA), D12.5 (GA), D12.6 (RA), D23.4 (BA), D23.5 (GA), D23.6 (RA), D24.4 (BA), D24.5 (GA), D24.6 (RA), J1.4, TP3.1, TP4.1, U1.1 (VIN), U1.3 (EN)

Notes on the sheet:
TSSI: Low -> Fault in BMS or IMD High -> No Fault RTML: Low -> TS ON High -> TS OFF

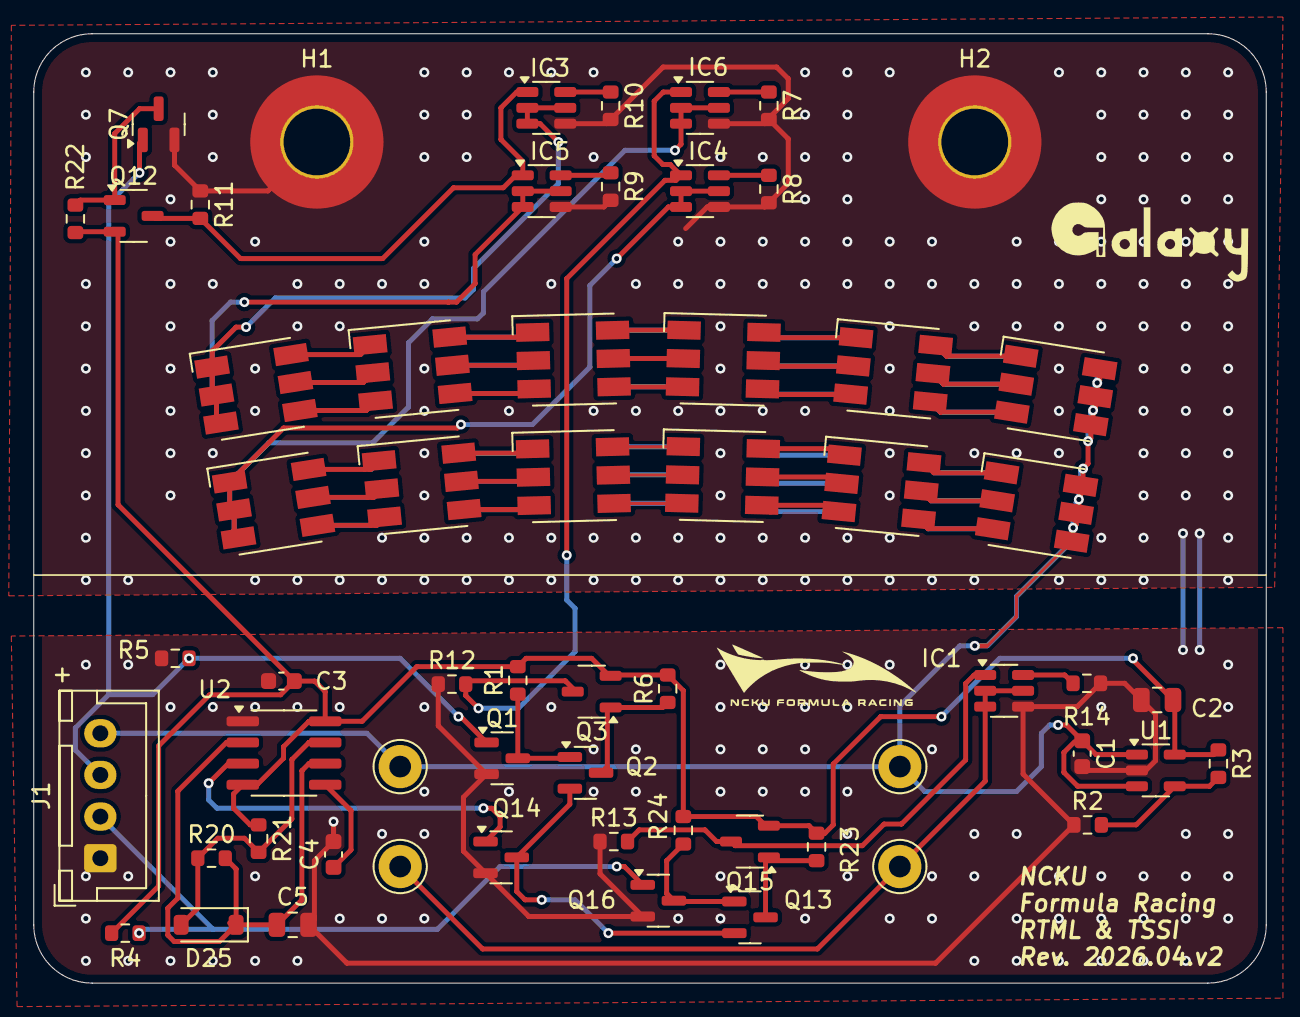
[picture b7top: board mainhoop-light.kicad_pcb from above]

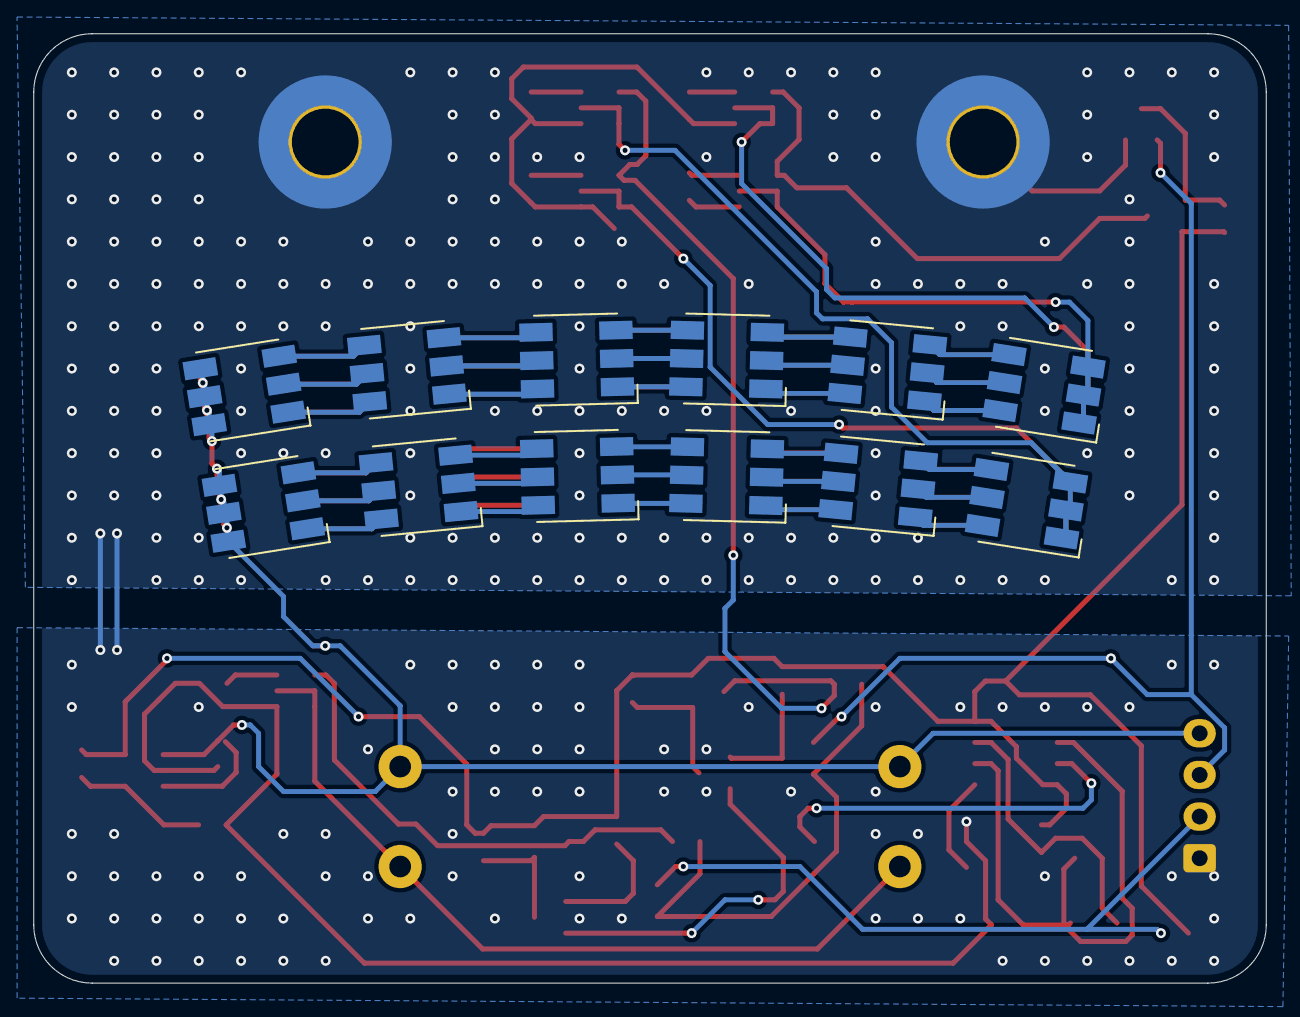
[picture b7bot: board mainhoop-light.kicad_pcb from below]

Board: 2 copper layers, 74.0 x 57.0 mm, 72 parts (12 on the bottom side), 89 nets.
